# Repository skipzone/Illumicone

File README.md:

# Illumicone
Illumicone interactive LED art project

www.illumicone.com

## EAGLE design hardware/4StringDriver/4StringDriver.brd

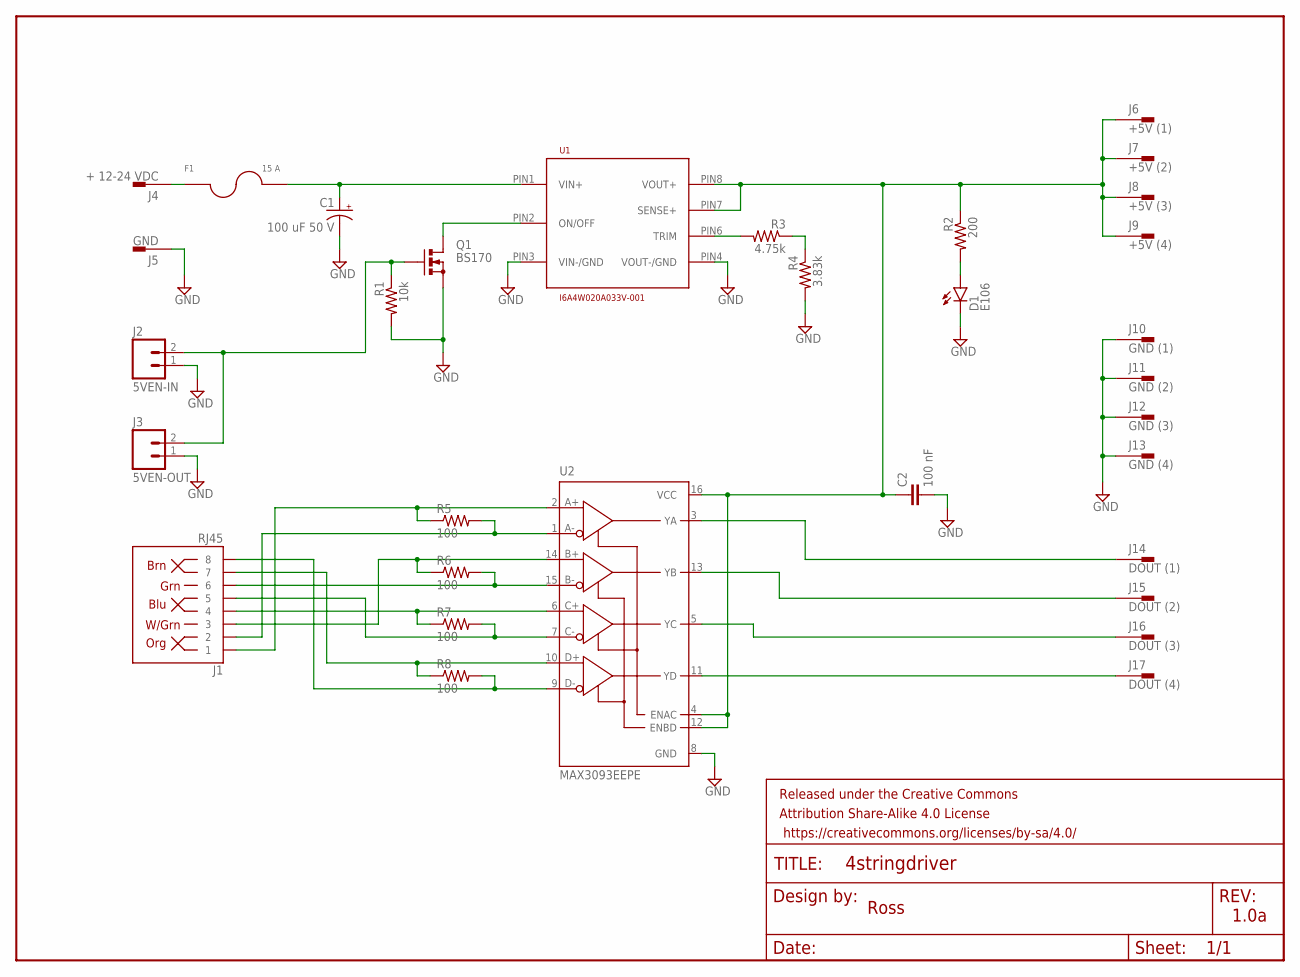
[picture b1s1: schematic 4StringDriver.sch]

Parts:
C1: 100 uF 50 V; E5-10,5
C2: 100 nF; CAP-PTH-SMALL-KIT
D1: E106; LED3MM
F1: 15 A; FUSE-ATM
FRAME1: FRAME-LETTER; CREATIVE_COMMONS
J1: RJ45; RJ45-8
J2: 5VEN-IN; JST-2-PTH-VERT
J3: 5VEN-OUT; JST-2-PTH-VERT
J4: + 12-24 VDC; F061.100
J5: GND; F061.100
J6: +5V (1); F061.100
J7: +5V (2); F061.100
J8: +5V (3); F061.100
J9: +5V (4); F061.100
J10: GND (1); F061.100
J11: GND (2); F061.100
J12: GND (3); F061.100
J13: GND (4); F061.100
J14: DOUT (1); F061.100
J15: DOUT (2); F061.100
J16: DOUT (3); F061.100
J17: DOUT (4); F061.100
Q1: BS170; SOT54E
R1: 10k; 0204/7
R2: 200; 0204/7
R3: 4.75k; 0204/7
R4: 3.83k; 0204/7
R5, R6, R7, R8: 100; R0603
U1: I6A4W020A033V-001; 16TH-BRICK-POWER-MODULE-NO-OPTIONS
U2: MAX3093EEPE; DIL16

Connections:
5VEN: J2.2, J3.2, Q1.G, R1.1
+5V: C2.1, J6.A1, J6.A2, J7.A1, J7.A2, J8.A1, J8.A2, J9.A1, J9.A2, R2.1, U1.PIN7 (SENSE+), U1.PIN8 (VOUT+), U2.4 (ENAC), U2.12 (ENBD), U2.16 (VCC)
DA+: J1.1, R5.1, U2.2 (A+)
DA-: J1.2, R5.2, U2.1 (A-)
DB+: J1.3, R6.1, U2.14 (B+)
DB-: J1.6, R6.2, U2.15 (B-)
DC+: J1.4, R7.1, U2.6 (C+)
DC-: J1.5, R7.2, U2.7 (C-)
DD+: J1.7, R8.1, U2.10 (D+)
DD-: J1.8, R8.2, U2.9 (D-)
DOUT1: J14.A1, J14.A2, U2.3 (YA)
DOUT2: J15.A1, J15.A2, U2.13 (YB)
DOUT3: J16.A1, J16.A2, U2.5 (YC)
DOUT4: J17.A1, J17.A2, U2.11 (YD)
GND: C1.-, C2.2, D1.K (C), J2.1, J3.1, J5.A1, J5.A2, J10.A1, J10.A2, J11.A1, J11.A2, J12.A1, J12.A2, J13.A1, J13.A2, Q1.S, R1.2, R4.2, U1.PIN3 (VIN-/GND), U1.PIN4 (VOUT-/GND), U2.8 (GND)
unnamed: Q1.D, U1.PIN2 (ON/OFF)
unnamed: D1.A, R2.2
unnamed: R3.2, U1.PIN6 (TRIM)
unnamed: R3.1, R4.1
VIN+: F1.PAD1 (1), F1.PAD2 (1), J4.A1, J4.A2
VIN+FUSED: C1.+, F1.PAD3 (2), F1.PAD4 (2), U1.PIN1 (VIN+)

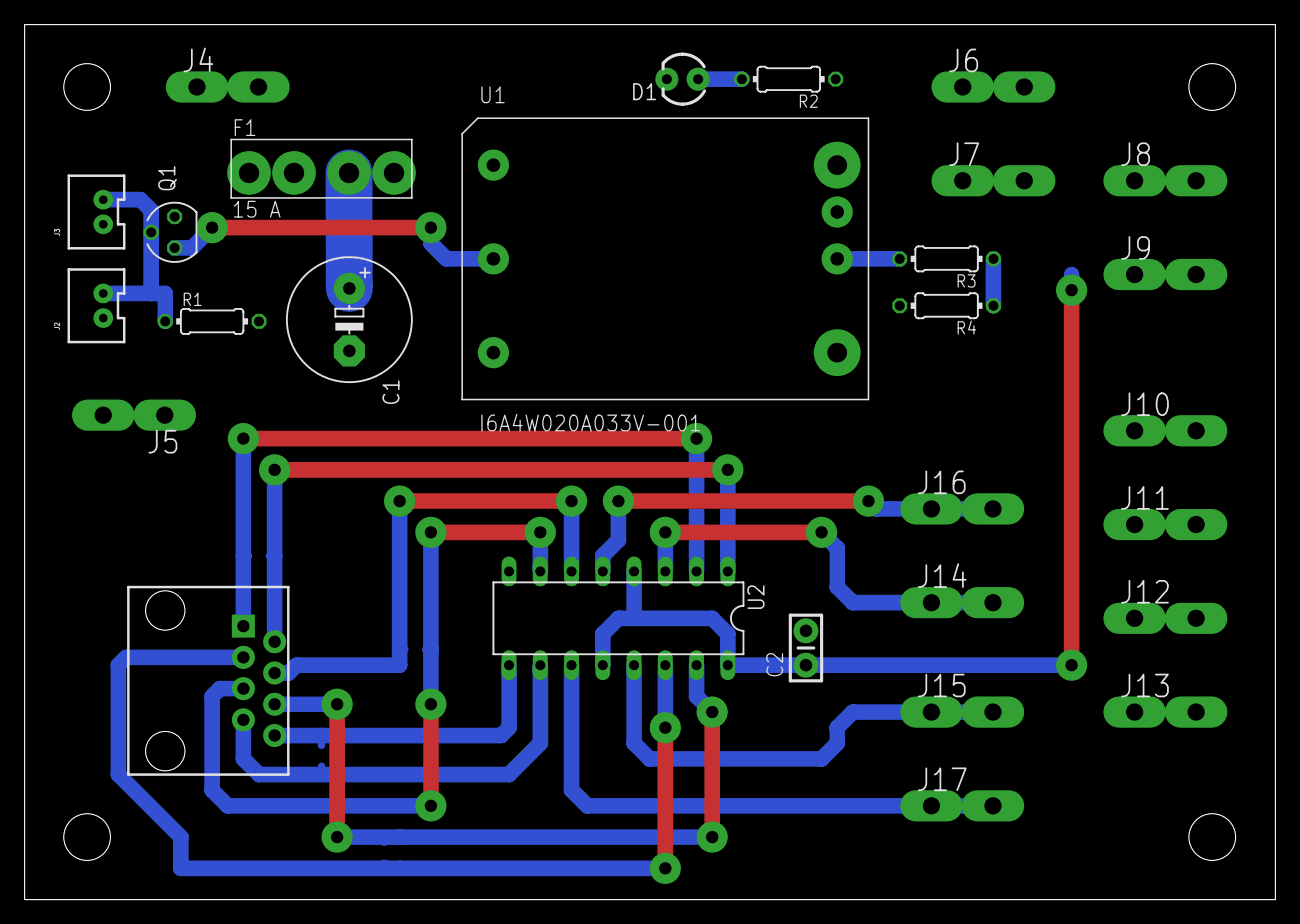
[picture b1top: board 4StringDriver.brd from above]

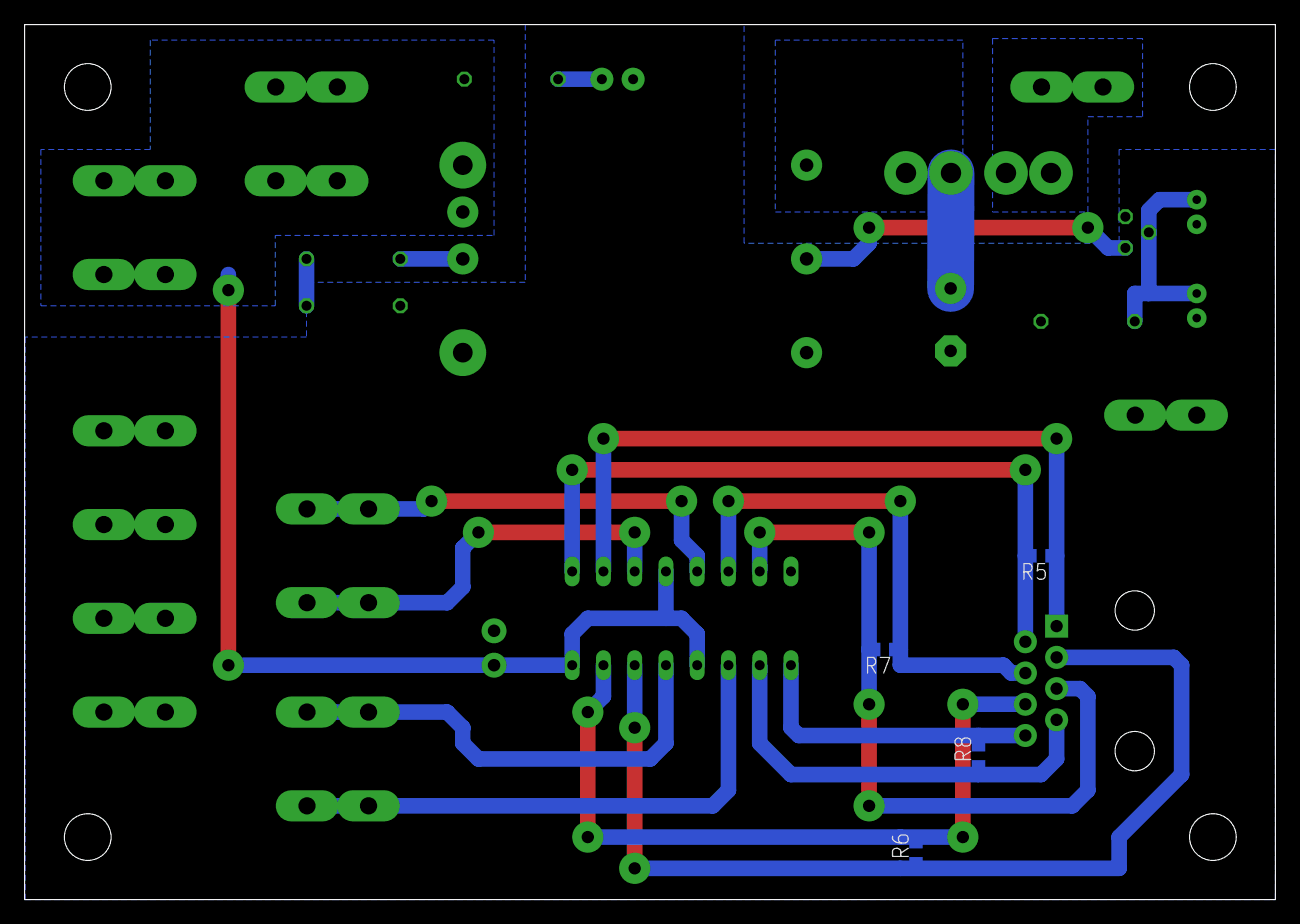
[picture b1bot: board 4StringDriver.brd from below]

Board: 2 copper layers, 101.7 x 71.1 mm, 33 parts (4 on the bottom side), 21 nets.

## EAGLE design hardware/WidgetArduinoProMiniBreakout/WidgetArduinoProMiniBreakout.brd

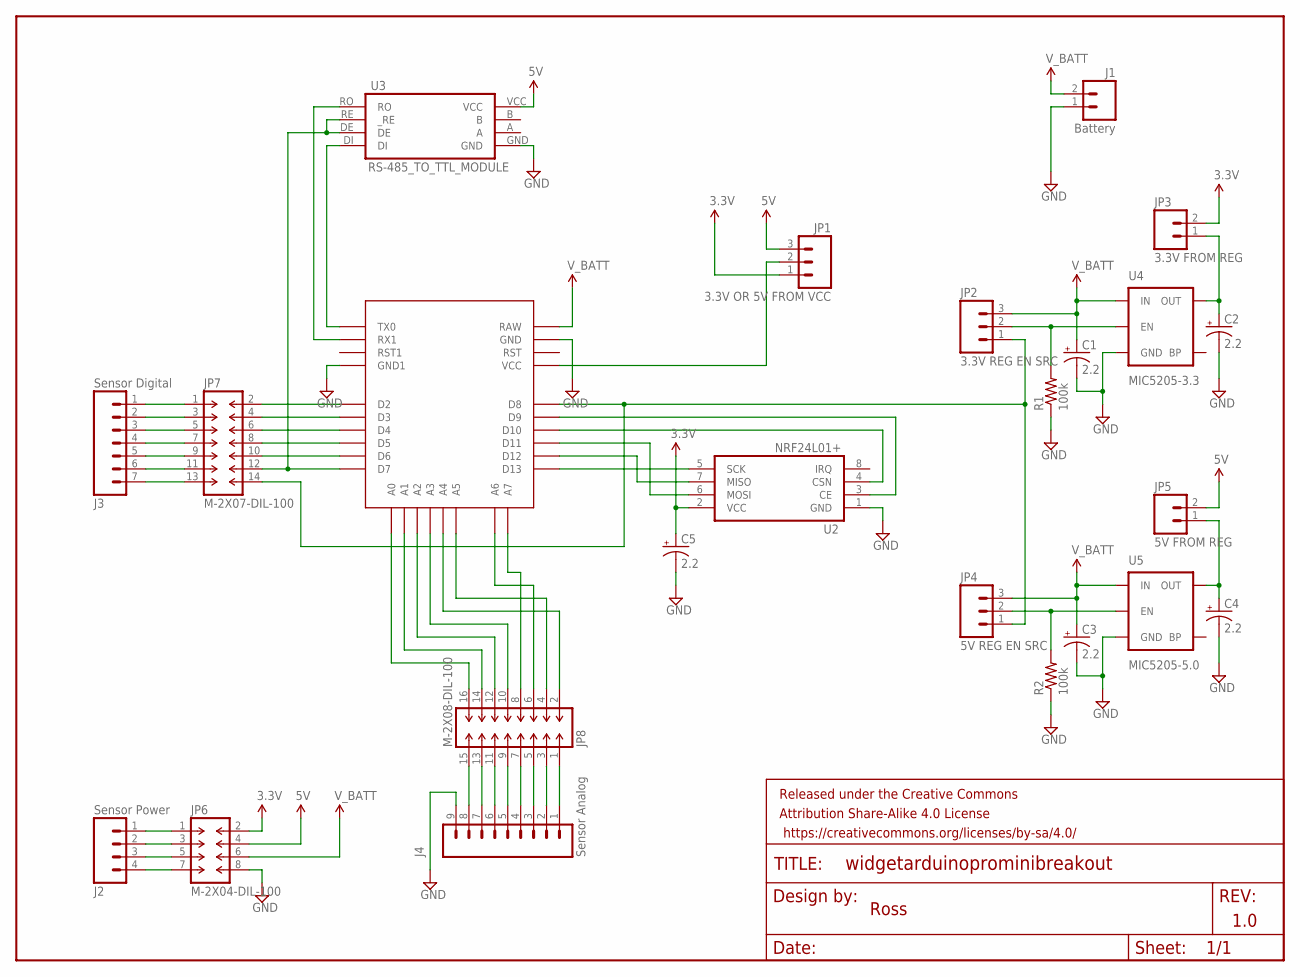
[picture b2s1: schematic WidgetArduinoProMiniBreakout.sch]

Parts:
C1, C2, C3, C4, C5: 2.2; SMC_A
FRAME1: FRAME-LETTER; CREATIVE_COMMONS
J1: Battery; JST-PH-2-TH-VERT
J2: Sensor Power; JST-PH-4-TH-VERT
J3: Sensor Digital; JST-PH-7-TH-VERT
J4: Sensor Analog; JST-PH-9-TH-VERT
JP1: 3.3V OR 5V FROM VCC; 1X03_LOCK_LONGPADS
JP2: 3.3V REG EN SRC; 1X03_LOCK_LONGPADS
JP3: 3.3V FROM REG; 1X02_LOCK_LONGPADS
JP4: 5V REG EN SRC; 1X03_LOCK_LONGPADS
JP5: 5V FROM REG; 1X02_LOCK_LONGPADS
JP6: M-2X04-DIL-100; DIL-100-2X04
JP7: M-2X07-DIL-100; DIL-100-2X07
JP8: M-2X08-DIL-100; DIL-100-2X08
R1, R2: 100k; R0603
U1: SPARKFUN_ARDUINO_PRO_MINI
U2: NRF24L01+; CHEAP_NRF24L01P_MODULE
U3: RS-485_TO_TTL_MODULE
U4: MIC5205-3.3; SOT23-5
U5: MIC5205-5.0; SOT23-5

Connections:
3.3V: C5.+, JP1.1, JP3.2, JP6.2, U2.2 (VCC)
5V: JP1.3, JP5.2, JP6.4, U3.VCC
A0: JP8.16, U1.A0
A0_J4: J4.8, JP8.15
A1: JP8.14, U1.A1
A1_J4: J4.7, JP8.13
A2: JP8.12, U1.A2
A2_J4: J4.6, JP8.11
A3: JP8.10, U1.A3
A3_J4: J4.5, JP8.9
A4_J4: J4.2, JP8.3
A5_J4: J4.1, JP8.1
A6: JP8.6, U1.A6
A6_J4: J4.4, JP8.7
A7: JP8.8, U1.A7
A7_J4: J4.3, JP8.5
D2: JP7.2, U1.D2
D2_J3: J3.1, JP7.1
D3: JP7.4, U1.D3
D3_J3: J3.2, JP7.3
D4: JP7.6, U1.D4
D4_J3: J3.3, JP7.5
D5: JP7.8, U1.D5
D5_J3: J3.4, JP7.7
D6: JP7.10, U1.D6
D6_J3: J3.5, JP7.9
D7: JP7.12, U1.D7, U3.DE, U3.RE (_RE)
D7_J3: J3.6, JP7.11
D8: JP2.1, JP4.1, JP7.14, U1.D8
D8_J3: J3.7, JP7.13
GND: C1.-, C2.-, C3.-, C4.-, C5.-, J1.1, J4.9, JP6.8, R1.1, R2.1, U1.GND, U1.GND1, U2.1 (GND), U3.GND, U4.2 (GND), U5.2 (GND)
unnamed: JP1.2, U1.VCC
unnamed: U1.D10, U2.4 (CSN)
unnamed: U1.TX0, U3.DI
unnamed: U1.D13, U2.5 (SCK)
unnamed: U1.D12, U2.7 (MISO)
unnamed: U1.D11, U2.6 (MOSI)
unnamed: U1.D9, U2.3 (CE)
unnamed: JP8.4, U1.A5
unnamed: JP2.2, R1.2, U4.3 (EN)
unnamed: C2.+, JP3.1, U4.5 (OUT)
unnamed: U1.RX1, U3.RO
unnamed: C4.+, JP5.1, U5.5 (OUT)
unnamed: JP4.2, R2.2, U5.3 (EN)
unnamed: JP8.2, U1.A4
unnamed: J2.1, JP6.1
unnamed: J2.2, JP6.3
unnamed: J2.3, JP6.5
unnamed: J2.4, JP6.7
V_BATT: C1.+, C3.+, J1.2, JP2.3, JP4.3, JP6.6, U1.RAW, U4.1 (IN), U5.1 (IN)

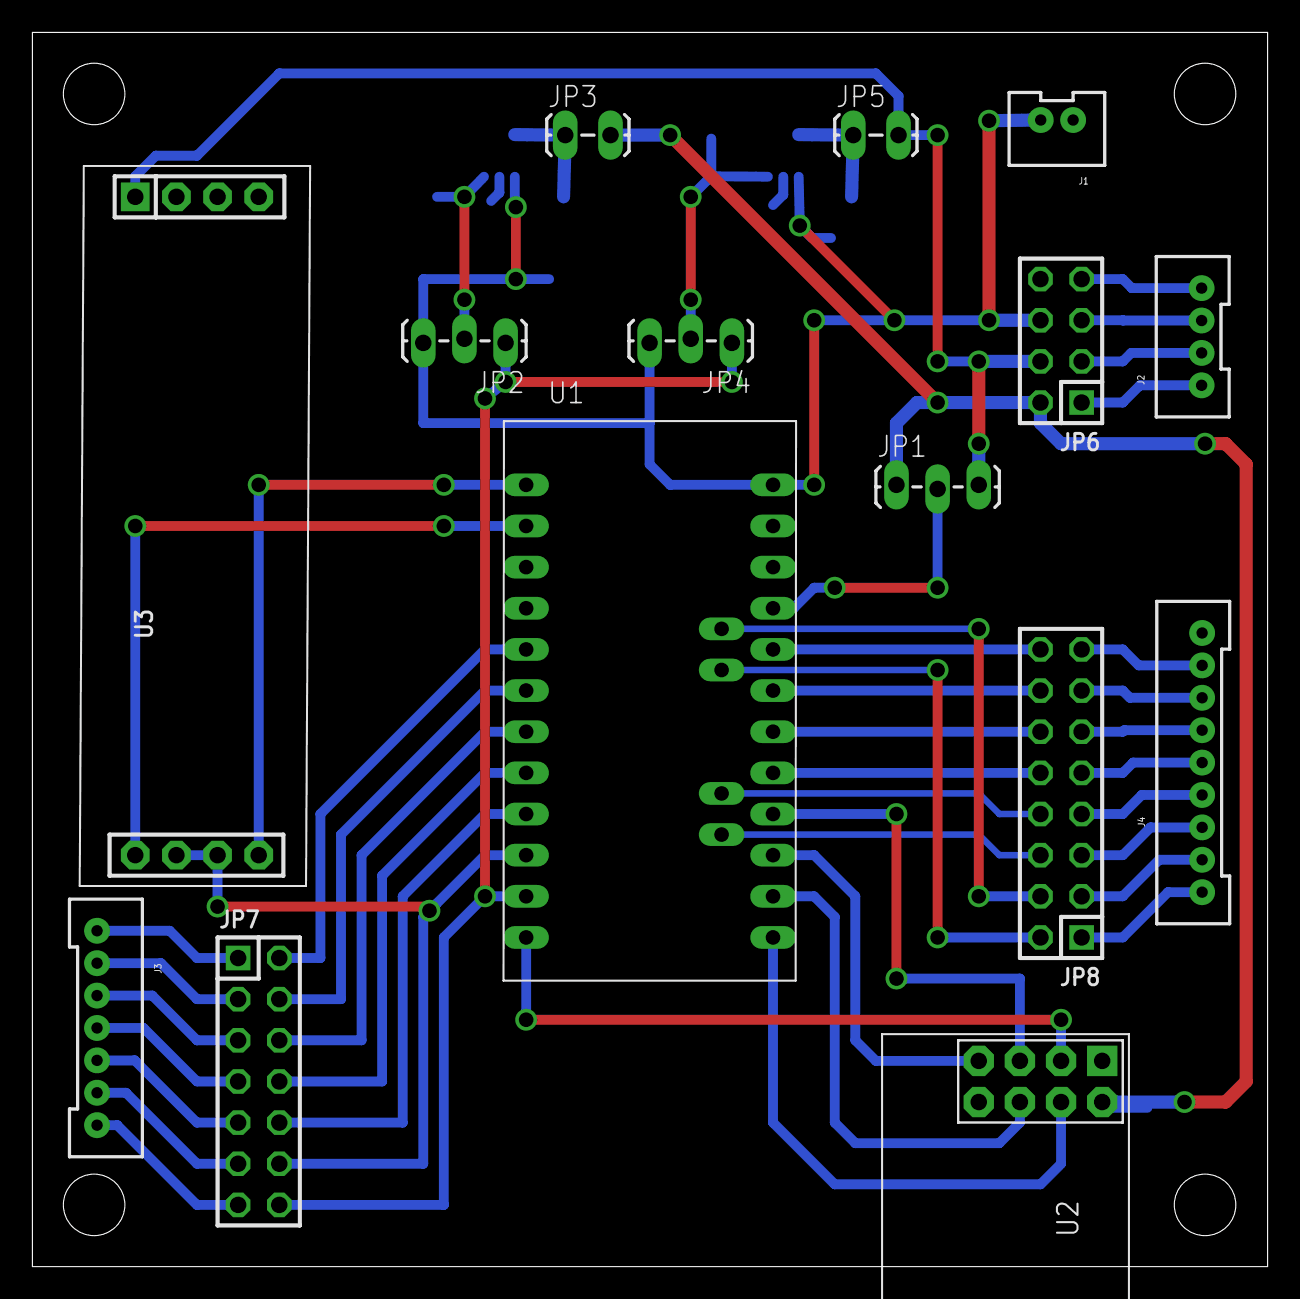
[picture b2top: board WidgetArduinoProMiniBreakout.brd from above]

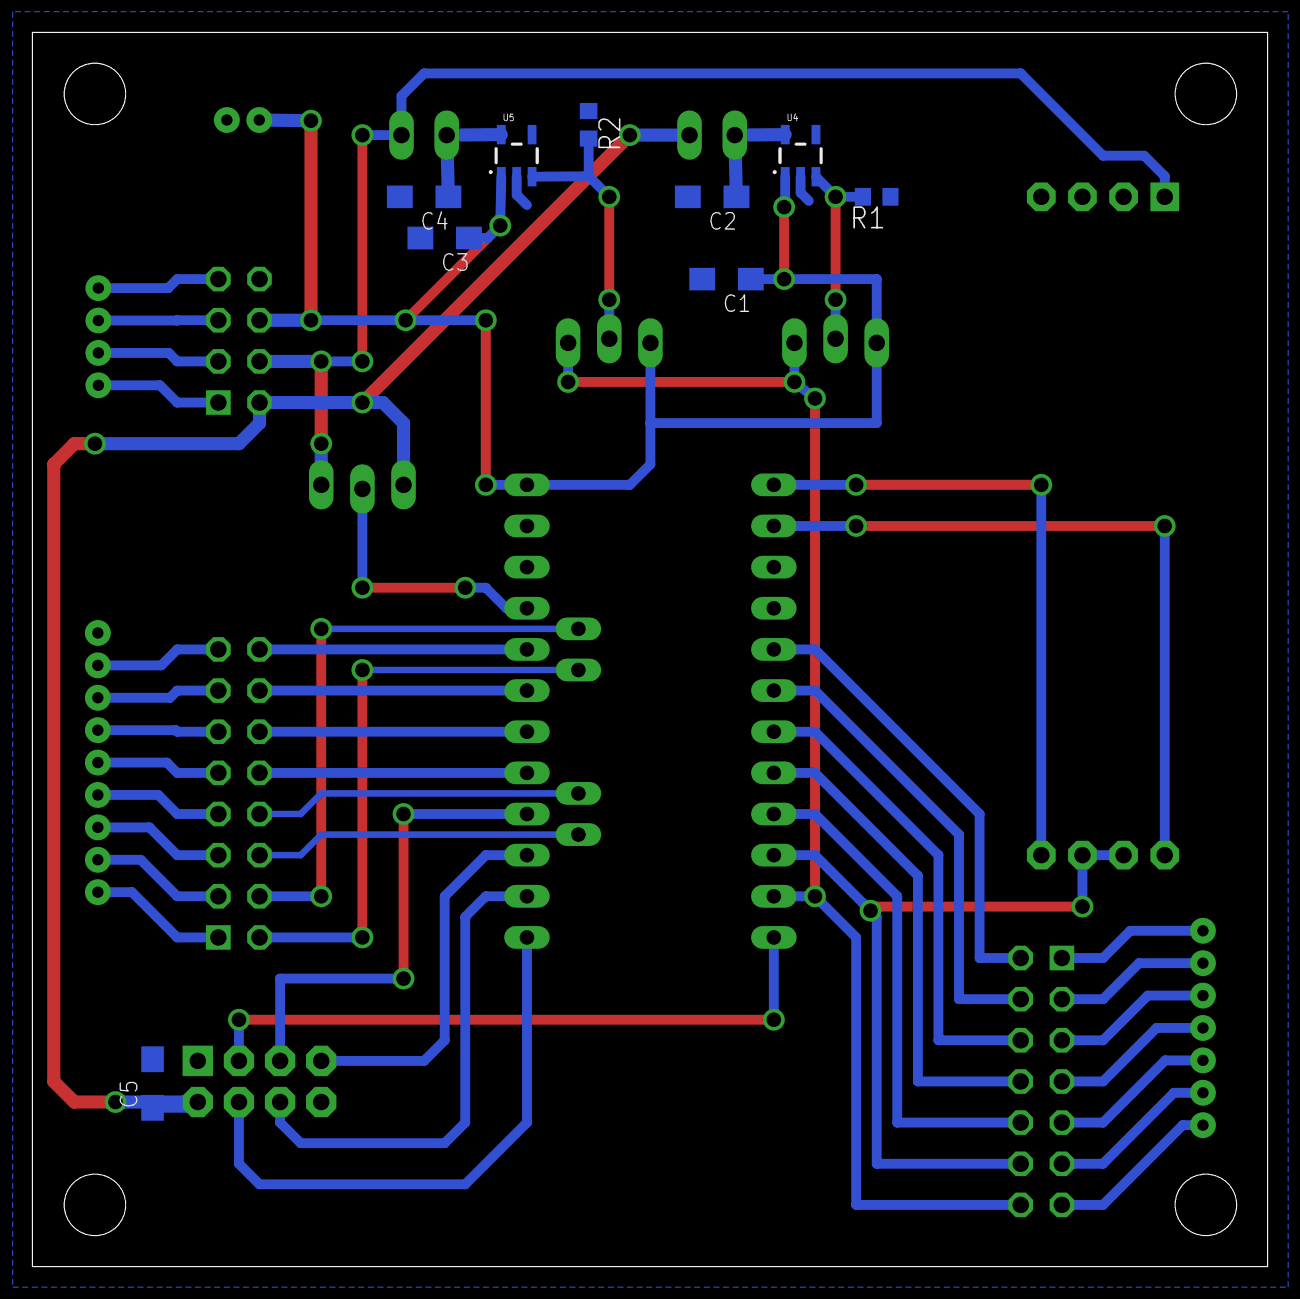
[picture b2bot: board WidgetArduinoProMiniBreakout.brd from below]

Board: 2 copper layers, 76.3 x 76.2 mm, 25 parts (9 on the bottom side), 50 nets.

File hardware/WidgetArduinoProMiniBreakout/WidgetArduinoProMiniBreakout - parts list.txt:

Partlist

Exported from WidgetArduinoProMiniBreakout.sch at 8/18/16 11:08 AM

EAGLE Version 7.5.0 Copyright (c) 1988-2015 CadSoft

Assembly variant: 

Part     Value                     Device                     Package                   Library             Sheet

C1       2.2                       CPOL-USSMCA                SMC_A                     rcl                 1
C2       2.2                       CPOL-USSMCA                SMC_A                     rcl                 1
C3       2.2                       CPOL-USSMCA                SMC_A                     rcl                 1
C4       2.2                       CPOL-USSMCA                SMC_A                     rcl                 1
C5       2.2                       CPOL-USSMCA                SMC_A                     rcl                 1
J1       Battery                   JST-PH-2                   JST-PH-2-TH-VERT          skipzone            1
J2       Sensor Power              JST-PH-4                   JST-PH-4-TH-VERT          skipzone            1
J3       Sensor Digital            JST-PH-7                   JST-PH-7-TH-VERT          skipzone            1
J4       Sensor Analog             JST-PH-9                   JST-PH-9-TH-VERT          skipzone            1
JP1      3.3V OR 5V FROM VCC       M03LOCK_LONGPADS           1X03_LOCK_LONGPADS        SparkFun-Connectors 1
JP2      3.3V REG EN SRC           M03LOCK_LONGPADS           1X03_LOCK_LONGPADS        SparkFun-Connectors 1
JP3      3.3V FROM REG             M02LOCK_LONGPADS           1X02_LOCK_LONGPADS        SparkFun-Connectors 1
JP4      5V REG EN SRC             M03LOCK_LONGPADS           1X03_LOCK_LONGPADS        SparkFun-Connectors 1
JP5      5V FROM REG               M02LOCK_LONGPADS           1X02_LOCK_LONGPADS        SparkFun-Connectors 1
JP6      M-2X04-DIL-100            M-2X04-DIL-100             DIL-100-2X04              con-headers-jp      1
JP7      M-2X07-DIL-100            M-2X07-DIL-100             DIL-100-2X07              con-headers-jp      1
JP8      M-2X08-DIL-100            M-2X08-DIL-100             DIL-100-2X08              con-headers-jp      1
R1       100k                      R-US_R0603                 R0603                     rcl                 1
R2       100k                      R-US_R0603                 R0603                     rcl                 1
U1       SPARKFUN_ARDUINO_PRO_MINI SPARKFUN_ARDUINO_PRO_MINI  SPARKFUN_ARDUINO_PRO_MINI skipzone            1
U2       NRF24L01+                 NRF24L01P_MODULECHEAPCHEAP CHEAP_NRF24L01P_MODULE    skipzone            1
U3       RS-485_TO_TTL_MODULE      RS-485_TO_TTL_MODULE       RS-485_TO_TTL_MODULE      skipzone            1
U4       MIC5205-3.3               MIC52053.3V                SOT23-5                   SparkFun-PowerIC    1
U5       MIC5205-5.0               MIC52055V                  SOT23-5                   SparkFun-PowerIC    1

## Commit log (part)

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2019-10-01 RF24 objects now instantiated during initialization.
2019-10-01 Added runLoop now supports multiple radios via pollRadio. Fixed various compilation errors.
2019-10-01 handleStressTestPayload now considers which radio a message was received on.
2019-10-24 Changed stats print interval from 1 to 5 seconds.
2019-10-24 Added helper script for starting widgetRcvr during development.
2019-10-24 Added pc helper script for running patternController during development.
2019-10-26 Added walkingPixel.py, which can be used for layout testing. It illuminates all pixels one-by-one.
2019-11-03 Added paths from environment variables.
2019-11-03 Fixed up some paths, cleaned up the steps for installing Arduino libraries.
2019-11-09 Added a generic Mini-Cone configuration.
2019-11-12 Added changes made on ic-widpatcon on 24 Aug. 2019 on playa.
2019-11-17 Added adm to list of groups that the user should be a member of.
2019-11-18 Modified widget message header to accommodate 32 widgets but only 4 channels per widget. Removed support for ContortOMatic and TriObelisk. Renumbered some widgets. Added 8 flower and 6 baton widgets.
2019-11-18 Widget id is now passed to constructor in order to facilitate using the same BatonWidget class for multiple baton widgets.
2019-11-18 FourPlay4xWidget replaces FourPlay42Widget and FourPlay43Widget.
2019-11-18 Changed id from 4 to 5 bits and channel from 3 to 2 bits. Also swapped the positions of channel and isActive.
2019-11-18 Added FlowerWidget class.
2019-11-18 Changed baton to baton1.
2019-11-18 Added six baton widgets and eight flower widgets.
2019-11-22 Moved Burning Man 2019 schedule to old.
2019-11-24 Updated widget ids.
2019-11-24 Added header that should have been in the initial commit.
2019-11-25 Renamed ...Baton spray pattern files to ...Baton1.
2019-11-25 New flower patterns.
2019-11-25 Yaw now normalized to 0-360 degrees. Gyro rotational speed (direction agnostic) now used for determining if the IMU is active. This allows the moving average length to be 1 (i.e., no averaging). Set 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
2019-11-25 Density now uses velocity instead of position.
2019-11-26 Did a quick hack to allow sharing widget channel 0 among all three colors.
2019-11-26 Now uses pattern include file.
2019-11-26 Code might be complete.
2019-11-26 Basic functionality is working. Not yet tested with a widget.
2019-11-27 Renamed schedule config file so all Winter Garden aGlow config files have the IBG (Idaho Botanical Garden) prefix. Reduced opacity and priority of rings-and-stripes pattern so that the particles from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
2019-11-27 Added shutdown for Wed. evening 27 Nov.
2019-11-28 Fixed name of coloredSprays_Baton1 pattern.
2019-11-30 Changed go-home quiescent start time to 20:50 and shutoff time to 21:00.
2019-12-01 Got it working.
2019-12-01 Initial evaluation of VL53L1X Time-of-Flight Distance Sensor at JUMP Maker Meetup in early November 2019.
2019-12-01 Moved GardenSpinner to Arduino.
2019-12-02 Fixed bug that caused zero acceleration values. Baton2 has a vibration sensor. Added optional skip of verifying MPU-6050 id (I2C address) because the goddamn counterfeit shit modules from Amaxon don'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
2019-12-02 Fixed channel number.
2019-12-07 Made the gold color more gold and less green.
2019-12-08 Added magenta/aqua sparkle pattern on Flower4 (Reiley's pretty, daisyish, rainbow-colored one).
2019-12-09 Changed mapping for new layout where all channels are used. Not compiled yet.
2019-12-09 Reduced the number of rings.
2019-12-10 Removed measurement averaging. Widget is active when TOF sensor gets a good reading.
2019-12-14 Added Lidar1 widget and LidarWidget class. Added white sparkle pattern on Lidar1. Removed Flower8.
2019-12-16 Added sudo to systemctl commands 'cause sometimes I get braindead then frustrated.
2019-12-16 Added configuration with ic2-strdrv IP address.
2019-12-17 Added entry for reading the CPU temperature on an RPi 4.
2019-12-17 Removed Flower8.
2019-12-22 Moved plotting to a separate function. y-axis label uses LaTeX for degree symbol.
2019-12-23 Added command-line options for widgetPortNumberBase and timeCompressionThresholdSeconds.
2020-01-12 Added test data file from WGaG.
2020-01-24 Created a rings-and-stripes pattern on Flower7 for Mini-Cone.
2020-02-22 Added a file for notes about resolving problems with the NRF24L01+ radio modules.
2020-02-26 Added StripePattern, which is being created from RgbStripePattern. It is still a work in progress and will not compile.
2020-02-29 Fixed name of hsvStr parameter.
2020-02-29 Both horizontal and vertical stripes work. Dynamically variable width works, but the sideband width can exceed the configured maximum. That bug also exists in RgbStripePattern. Variable hue and hue g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
2020-02-29 Added config for rings on Flower3 and Flower4.
2020-02-29 Added RattleWidget, which, at this point, is just a clone of BatonWidget and has exactly the same behavior. Added Rattle1 and Rattle2. Removed Baton3-Baton6 because we're not going to make more becau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
2020-03-01 Swapped Flower3 and Flower6. 3 is now assigned to the spring rotation, and 6 is now assigned to the rings. Changed the number of vertical stripes from 12 to 4.
2020-03-02 Changed data rate to 250 kbps and power level to low.
2020-03-02 Removed batons 3 through 6 and added rattles 1 and 2. Not compiled or tested yet.
2020-03-03 Added configuration for dynamic hue and saturation. Compiles, but not tested.
2020-03-04 Implemented measurement mapper, hue, and saturation. Tested with vertical stripes only.
2020-03-04 Added multicolor sparkle on Rattle2.
2020-03-05 Enabled Rattle1 for color change.
2020-03-05 Updated to match spring_Flower5_Flower3_Rattle1.
2020-03-10 Added command for restarting NTP server.
2020-11-22 Created 2020 config for Winter Garden aGlow at Idaho Botanical Garden. At present, just has shutdown at 21:45.
2020-11-24 Added the 2020 pattern configuration for IBG, which, at present, is the same as the 2019 configuration.
2020-11-24 Fixed jump/discontinuity in rings_Flower2.
    The number of green rings was 3, which is not a factor of 100. Changed pattern
    to have 1 red, 2 green, and 4 blue rings.
2020-11-26 Added tailm to aliases. Updated install docs for adding illumicone to adm group.
2021-10-02 Moved Illumibrate 2020 config files to old dir.
2021-10-16 Added GitHub credential setup.
2021-10-16 Added note about GitHub user name coming from the personal authorization token.
2021-11-02 Added ICSM_Test Arduino sketch to do initial hardware testing of the Illumicone Controller System Manager prototype.
2021-11-05 Cloned Widget_Mike.ino from Widget_FourPlay.ino.
2021-11-06 Added radio number field to testData/rainstick.log for compatibility with current widgetPlayback.py.
2021-11-06 Added information specific to the Zero 2 W.
2021-11-06 A little turd pre-polishing.
2021-11-08 Fixed problems with paths containing spaces. Added -r option so directories will get copied.
2021-11-19 Updated schedule for IBG 2021. Added widget and pattern plan. IBG configs still untested.
2021-11-21 Added equality and inequality operators to SchedulePeriod.
2021-11-22 Configuration for IBG 2021 pattern set 1.
2021-11-22 Added blue, gold, green, red, and white sparkle patterns for Mike1.
2021-11-22 Added rain and spray patterns for Mike2.
2021-11-22 Moved Alvord 2021 config to old.
2021-11-23 Added config for widgetRcvr3, but it turns out we don't need it because fixing up the radio config made the flower widgets work great.
2021-11-23 Changed the flowers to use acks, 250 mbps, and high power (instead of max), which tremendously helped with throughput.
2021-11-25 Swapped radios 0 and 1. 0 now on ch. 97, 1 on ch. 76.
2021-12-12 Added single stripe with color controlled by rotational velocity for Flower7.
2021-12-24 Combined Baton and Rattle configurations into BatRat.
2021-12-25 Repurposed Flower4 for blue rain.
2021-12-26 Put Baton2 on red, green, and gold.
2022-01-01 Added hard reset of MPU6050 by power cycling it. Needs some cleanup.
2022-01-01 Switched to pattern set 4 for a final-night test of a MIke widget prototype (which was successful).
2022-01-01 Added git notes doc.
2022-01-16 Updated radio config. LED now shows blue for inactive, green for active, and red for TX error.
2022-01-24 Renamed SwitchPotBox to PotBox.
2022-01-29 Added new Widget_Pump, which replaces Widget_Plunger. Still a messy draft. Does not compile.
2022-06-19 Moved IBG 2021 configs to the 'old' directory.
2022-07-12 Updated wireless configuration data rate and power for compatibility with current cone configuration.
2022-07-21 Added workaround for disabling dhclient on ic-strdrv to prevent the static IP address from changing. Added backup of the illumicone router.
2022-08-21 Modified BatRat3 to use the IMU power pin and watchdog reset, just like BatRat2. Modified BoogieBoard to use the same controller board as BatRat2 and BatRat3.
2022-08-22 Added support for override periods to facilitate forcing the cone active during development, setup, etc.
2023-02-17 Modified schedule on 1 Sept. on playa: The sun went behind the mountain at 19:08 PDT.
2023-02-17 Added IP address for amos.
2023-02-17 Added a note about how to fix a stale githubcli-archive-keyring.gpg.
2023-02-17 Added widget receiver 2. Set pattern controller address for JUMP installation.
2023-02-21 Fixed UDP typo in OPC bytes-sent error message.
2023-02-24 Renamed Baton and Rattle widgets to BatRat. Added batrat5.
2023-02-24 Added ENABLE_SYSTEM_RESET_WATCHDOG and IMU_POWER_PIN for all the BatRats.
2023-02-24 Renamed spray gold, green, and red for Baton2 to be for BatRat2.
2023-02-25 Made the 25 Feb. setup override period start eariler because the daytime dryout mode uses about 490 watts, which is a helluva load when combined with the mini-split heater at the end of an extension 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
2023-02-26 Added indications of Flower1 and Flower4 being located in the vestibule. Removed PotBox/FourPlay42 hack.
2023-03-01 Replaced pre-midnight and nighttime shutoff periods with pre-midnight and nighttime blue.
2023-03-03 Renamed stripes_Flower6 and stripes_Flower7.
2023-03-03 Added magenta sparkle on BatRat1.
2023-03-03 Added spinner blocks on Flower3. Might work.
2023-03-03 Added positionDivisor to Spinner pattern.
2023-03-04 Final schedule for Illumibrate night and probably the following week.
2023-06-15 Moved Illumibrate 2023 config to old directory.
2023-06-15 Added Eye and Schroeder's. Removed BoogieBoard.
2023-11-06 Started edits for setup with Bullseye RPi OS.
2023-12-30 ILLUMICONE... environment variables need to be defined in .profile so that the readCpuTemperature cron job will work.
2024-06-14 Moved Element 11 2023 configs to old.
2025-05-30 Moved Burning Man 2024 config files to old.
2025-05-30 Added RGB LED to Widget_StressTest.
2025-06-03 Added several links and what hopefully is the original useful information (which is now a dead link in the original, linked article).
2025-06-04 Fixed ScotchHop TX failure (red) LED flash when in standby mode. Step ID now read from jumpers.
2025-06-12 Adjusted ScotchHop widget tx interval, inactivity timeout, and activity hang time.
2025-06-18 Added scotchHop4Pride to pattern set 1.
2025-06-20 E11 Friday night patterns. Added scotchHop8PrideFlashing.
2025-06-27 Added commented-out addresses for MeowStar and meow.
2025-11-02 Added TCP support to stringTester.
2026-05-22 Shebang now says python3.
2026-05-22 Minor edits. Validated a few more sections.
2026-05-22 clang pragma now conditional on __clang__.
2026-05-22 Turned off ScotchHop simulated measurements.
2026-05-24 Audio output works, but decay does not sound natural.
2026-05-24 Added secondary resonance. Windchime config now in json.

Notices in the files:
parts and their libraries:
SparkFun-Aesthetics: Licensing: Creative Commons ShareAlike 4.0 International - https://creativecommons.org/licenses/by-sa/4.0
SparkFun-Aesthetics: Released under the Creative Commons Attribution Share-Alike 4.0 License
SparkFun-Aesthetics: https://creativecommons.org/licenses/by-sa/4.0
